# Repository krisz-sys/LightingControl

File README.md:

How it works?

The ESP8266 runs a web server. The microcontroller controls LED lighting and an electric valve.

The microcontroller handles the following tasks:
  The user can adjust the LED lighting using either the slider or the potentiometer.
  The valve was controlled based on the temperature measured on the radiator

You can access the web server by entering the IP address into your browser: http://192.168.1.230/ .
Additionally, you need to configure the WiFi SSID and password.

You can see the circuit schematic below:

<br>

<br>
Here is the PCB layout:
<br>

<br>
You can find the AutoCAD Eagle design files as LightController_PCB.

If the web server is live, you should see the following view. The most important elements are the slider, the temperature value:
<br>

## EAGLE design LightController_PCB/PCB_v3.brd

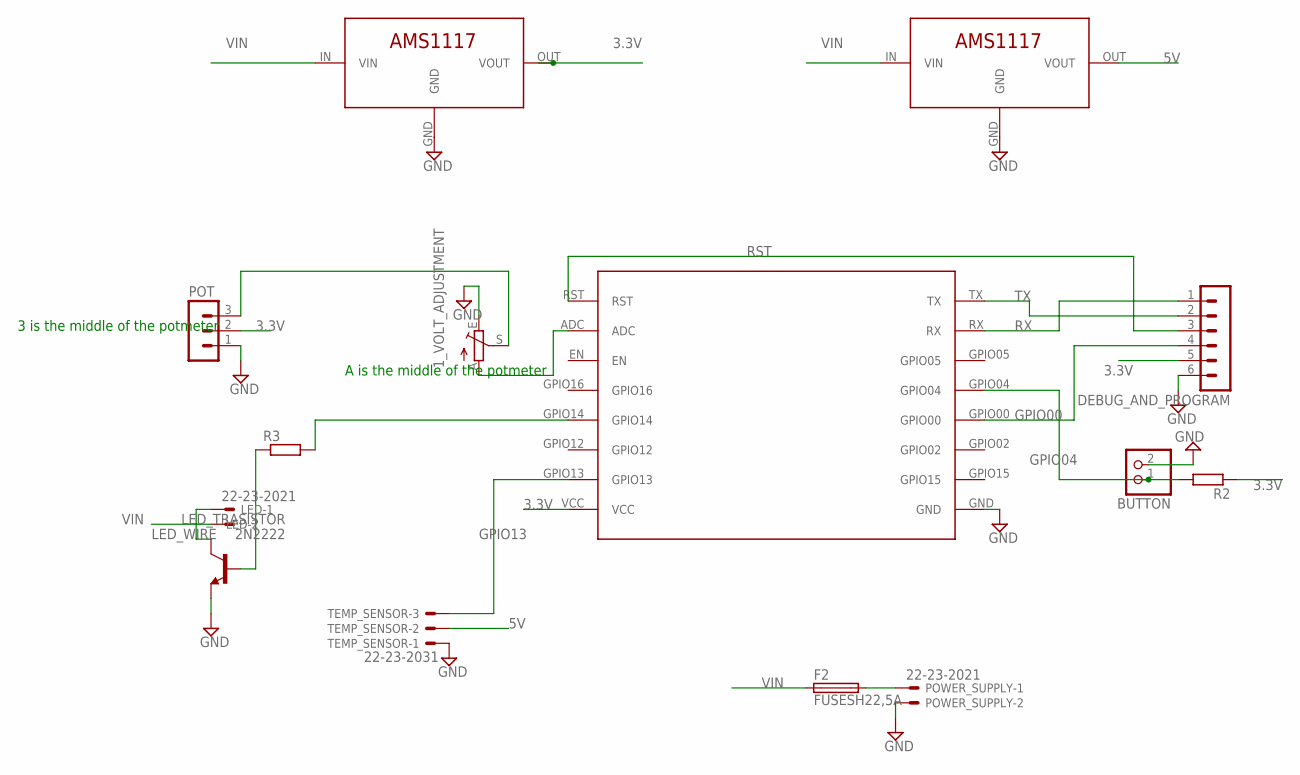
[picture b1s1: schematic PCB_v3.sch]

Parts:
1_VOLT_ADJUSTMENT: TRIM_EU-CA6V; CA6V
3.3V_REGULATOR, 5V_REGULATOR: AMS1117
BUTTON: PINHD-1X2; 1X02
DEBUG_AND_PROGRAM: MA06-1
F2: FUSESH22,5A; SH22,5A
LED: 22-23-2021
LED_TRASISTOR: 2N2222
POT: MA03-1
POWER_SUPPLY: 22-23-2021
R2, R3: R-EU_0309/12; 0309/12
TEMP_SENSOR: 22-23-2031
U$1: ESP8266

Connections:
3.3V: 3.3V_REGULATOR.OUT (VOUT), DEBUG_AND_PROGRAM.5, POT.2, R2.1, U$1.VCC
5V: 5V_REGULATOR.OUT (VOUT), TEMP_SENSOR.2
GND: 1_VOLT_ADJUSTMENT.E, 3.3V_REGULATOR.GND, 5V_REGULATOR.GND, BUTTON.2, DEBUG_AND_PROGRAM.6, LED_TRASISTOR.E, POT.1, POWER_SUPPLY.2, TEMP_SENSOR.1, U$1.GND
GPIO00: DEBUG_AND_PROGRAM.4, U$1.GPIO00
GPIO04: BUTTON.1, R2.2, U$1.GPIO04
GPIO13: TEMP_SENSOR.3, U$1.GPIO13
LED_WIRE: LED.1, LED_TRASISTOR.C
unnamed: 1_VOLT_ADJUSTMENT.A, U$1.ADC
unnamed: 1_VOLT_ADJUSTMENT.S, POT.3
unnamed: F2.2, POWER_SUPPLY.1
unnamed: R3.2, U$1.GPIO14
unnamed: LED_TRASISTOR.B, R3.1
RST: DEBUG_AND_PROGRAM.3, U$1.RST
RX: DEBUG_AND_PROGRAM.1, U$1.RX
TX: DEBUG_AND_PROGRAM.2, U$1.TX
VIN: 3.3V_REGULATOR.IN (VIN), 5V_REGULATOR.IN (VIN), F2.1, LED.2

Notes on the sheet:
3 is the middle of the potmeter
A is the middle of the potmeter

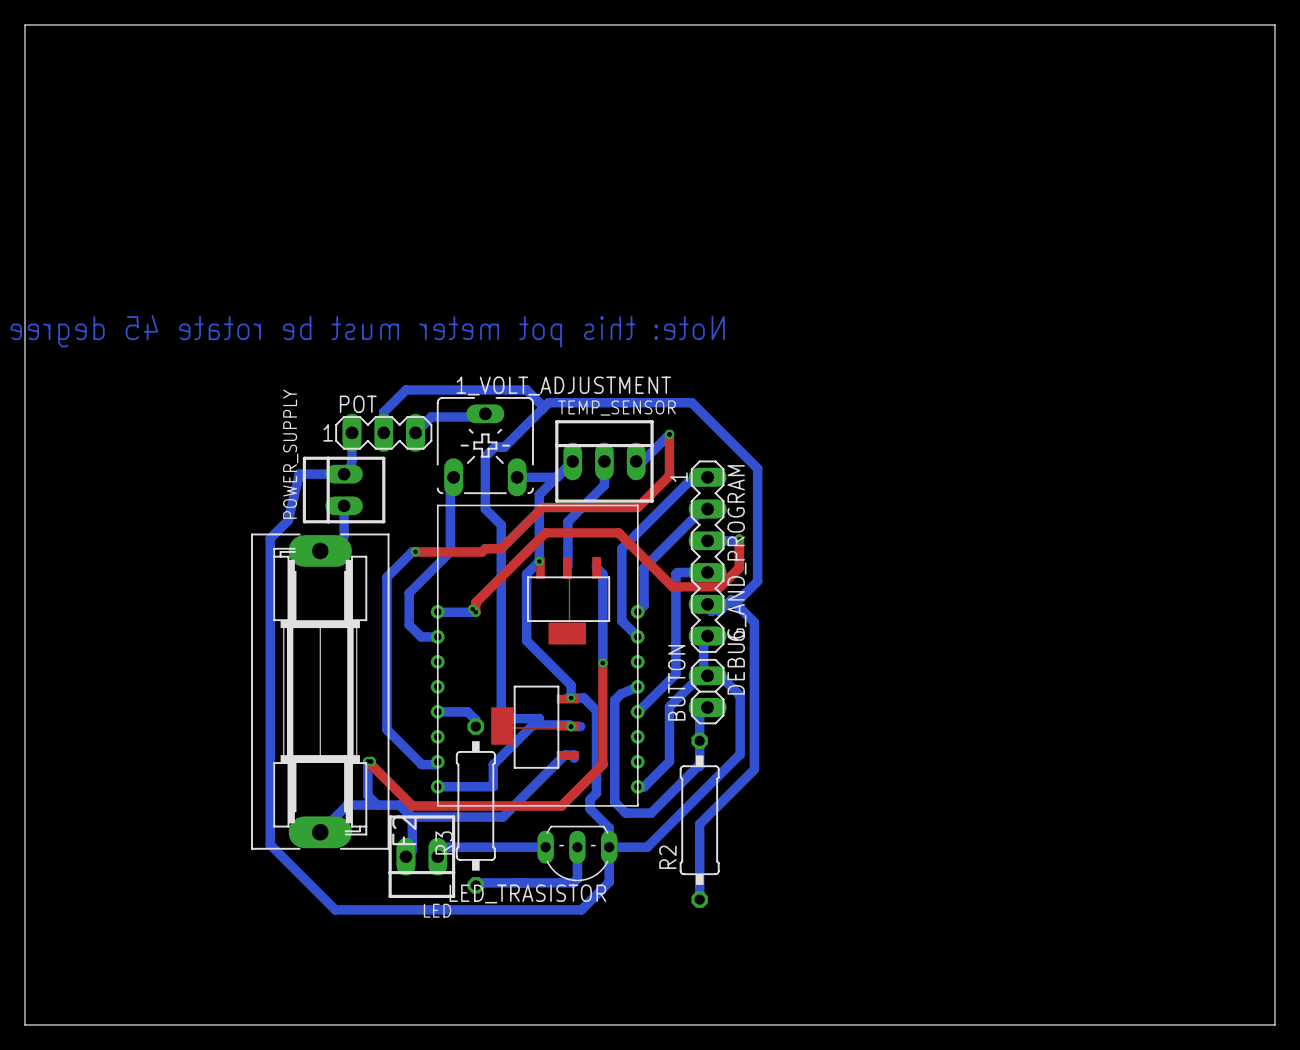
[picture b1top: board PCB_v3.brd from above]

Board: 2 copper layers, 100.0 x 80.0 mm, 14 parts (0 on the bottom side), 16 nets.
